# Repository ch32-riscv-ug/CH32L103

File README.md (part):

# CH32L103

<!-- This file is generated from ch32-riscv-ug/ch32-device-data (index/ + evidence/ + pipeline/build/build_readme.py). Edit there, not here. -->

[Choose a part](#product-comparison) &middot; [Documents](#documents) &middot; [Pin maps](#pin-maps--alternate-functions) &middot; [Pin viewer](https://ch32-riscv-ug.github.io/ch32-device-data/pins.html?chip=CH32L103) &middot; [Errata](#errata) &middot; [Examples](#evt-examples) &middot; [Address map](#address-map)

## Quick start

Programming and debug: **2-wire SDI** (WCH-Link, `Serial Debug Interface`).

### Debug / serial defaults

Where these land **without writing a remap register**. SWD is live at reset; the UART pads are not -- the pin must still be put into alternate-function mode. See `route` in evidence/README.ja.md.

| Series | SWDIO | SWCLK | UART TX | UART RX |
|---|---|---|---|---|
| CH32L103 | PA13 | PA14 | PA9 (USART1); PA2 (USART2) | PA10 (USART1); PA3 (USART2) |
| CH32M103 | PA13 | PA14 | PA2 (USART2); PB10 (USART3) | PA3 (USART2); PB11 (USART3) |

### Datasheets and reference manual

- CH32L103DS0.PDF (datasheet): [English](https://ch32-riscv-ug.github.io/CH32L103/datasheet_en/CH32L103DS0.PDF) · [中文](https://ch32-riscv-ug.github.io/CH32L103/datasheet_zh/CH32L103DS0.PDF)
- CH32L103RM.PDF (reference manual): [English](https://ch32-riscv-ug.github.io/CH32L103/datasheet_en/CH32L103RM.PDF) · [中文](https://ch32-riscv-ug.github.io/CH32L103/datasheet_zh/CH32L103RM.PDF)

## Series

| Series | Core | ISA | Flash | SRAM | Main clock | VDD | Packages | Products | Official |
|---|---|---|---|---|---|---|---|---|---|
| **CH32L103** | QingKe V4C | RV32IMAC | 64K | 20K | 96 MHz | 1.8-3.6V | LQFP48,QFN20,QFN32,QSOP28,TSSOP20 | 6 | [en](https://www.wch-ic.com/products/CH32L103.html) / [zh](https://www.wch.cn/products/CH32L103.html) |
| **CH32M103** | QingKe V4C | RV32IMAC | 64K | 20K | 96 MHz | 1.8-3.6V | QSOP28 | 1 | [en](https://www.wch-ic.com/products/CH32M103.html) / [zh](https://www.wch.cn/products/CH32M103.html) |

## Product comparison

### CH32L103 product comparison

Only the 11 rows that differ between these 6 products; the other 14 are the same for all of them.

| | [CH32L103&#8203;C8T6](https://ch32-riscv-ug.github.io/ch32-device-data/pins.html?chip=CH32L103C8T6)&#8203;(LQFP48) | [CH32L103&#8203;F8P6](https://ch32-riscv-ug.github.io/ch32-device-data/pins.html?chip=CH32L103F8P6)&#8203;(TSSOP20) | [CH32L103&#8203;F8U6](https://ch32-riscv-ug.github.io/ch32-device-data/pins.html?chip=CH32L103F8U6)&#8203;(QFN20) | [CH32L103&#8203;G8R6](https://ch32-riscv-ug.github.io/ch32-device-data/pins.html?chip=CH32L103G8R6)&#8203;(QSOP28) | [CH32L103&#8203;K8U6](https://ch32-riscv-ug.github.io/ch32-device-data/pins.html?chip=CH32L103K8U6)&#8203;(QFN32) | [CH32L103&#8203;K8U7](https://ch32-riscv-ug.github.io/ch32-device-data/pins.html?chip=CH32L103K8U7)&#8203;(QFN32) |
|---|---|---|---|---|---|---|
| **GPIO** | 37 | 16 | 19 | 26 | 31 | 31 |
| **Temperature** | -40..85C | -40..85C | -40..85C | -40..85C | -40..85C | -40..105C |
| ADC | 10+3 | 9+3 | 10+3 | 10+3 | 10+3 | 10+3 |
| Tkey | 10 | 9 | 10 | 10 | 10 | 10 |
| CMP | 3 | CMP1 CMP2 | 3 | 3 | 3 | 3 |
| SPI | 2 | SPI1 | 2 | 2 | SPI1 | SPI1 |
| I2C | 2 | I2C1 | 2 | 2 | I2C1 | I2C1 |
| CAN FD | √ | - | - | - | √ | - |
| USB Host Device | Host Device | Device | Host Device | Host Device | Host Device | Host Device |
| USB PD Type-C | DRP Source Sink | DRP Source Sink | DRP Source Sink Built-in Rd(1) | DRP Source Sink | DRP Source Sink Built-in Rd(1) | DRP Source Sink Built-in Rd(1) |
| Main applications and features | General-purpose, Pin compatible | General-purpose, Pin compatible | General-purpose, pin optimized | General-purpose, motor master | General-purpose, pin optimized | General-purpose, pin optimized |

<details><summary>All 25 rows</summary>

| | [CH32L103&#8203;C8T6](https://ch32-riscv-ug.github.io/ch32-device-data/pins.html?chip=CH32L103C8T6)&#8203;(LQFP48) | [CH32L103&#8203;F8P6](https://ch32-riscv-ug.github.io/ch32-device-data/pins.html?chip=CH32L103F8P6)&#8203;(TSSOP20) | [CH32L103&#8203;F8U6](https://ch32-riscv-ug.github.io/ch32-device-data/pins.html?chip=CH32L103F8U6)&#8203;(QFN20) | [CH32L103&#8203;G8R6](https://ch32-riscv-ug.github.io/ch32-device-data/pins.html?chip=CH32L103G8R6)&#8203;(QSOP28) | [CH32L103&#8203;K8U6](https://ch32-riscv-ug.github.io/ch32-device-data/pins.html?chip=CH32L103K8U6)&#8203;(QFN32) | [CH32L103&#8203;K8U7](https://ch32-riscv-ug.github.io/ch32-device-data/pins.html?chip=CH32L103K8U7)&#8203;(QFN32) |
|---|---|---|---|---|---|---|
| **Flash** | 64K | 64K | 64K | 64K | 64K | 64K |
| **SRAM** | 20K | 20K | 20K | 20K | 20K | 20K |
| **GPIO** | 37 | 16 | 19 | 26 | 31 | 31 |
| **Temperature** | -40..85C | -40..85C | -40..85C | -40..85C | -40..85C | -40..105C |
| Advanced-control TIM1 (16-bit) | 1 | 1 | 1 | 1 | 1 | 1 |
| General-purpose TIM2/3 (16-bit) | 2 | 2 | 2 | 2 | 2 | 2 |
| General-purpose TIM4 (32-bit) | 1 | 1 | 1 | 1 | 1 | 1 |
| Low-power timer (LPTIM) | √ | √ | √ | √ | √ | √ |
| Timer Watchdog | 2 ( WWDG + IWDG ) | 2 ( WWDG + IWDG ) | 2 ( WWDG + IWDG ) | 2 ( WWDG + IWDG ) | 2 ( WWDG + IWDG ) | 2 ( WWDG + IWDG ) |
| SysTick (64-bit) | √ | √ | √ | √ | √ | √ |
| RTC | √ | √ | √ | √ | √ | √ |
| ADC | 10+3 | 9+3 | 10+3 | 10+3 | 10+3 | 10+3 |
| Tkey | 10 | 9 | 10 | 10 | 10 | 10 |
| OPA | 1 | 1 | 1 | 1 | 1 | 1 |
| CMP | 3 | CMP1 CMP2 | 3 | 3 | 3 | 3 |
| USART | 4 | 4 | 4 | 4 | 4 | 4 |
| SPI | 2 | SPI1 | 2 | 2 | SPI1 | SPI1 |
| I2C | 2 | I2C1 | 2 | 2 | I2C1 | I2C1 |
| CAN | 1 | 1 | 1 | 1 | 1 | 1 |
| CAN FD | √ | - | - | - | √ | - |
| USB Host Device | Host Device | Device | Host Device | Host Device | Host Device | Host Device |
| USB PD Type-C | DRP Source Sink | DRP Source Sink | DRP Source Sink Built-in Rd(1) | DRP Source Sink | DRP Source Sink Built-in Rd(1) | DRP Source Sink Built-in Rd(1) |
| CPU main frequency | Max: 96MHz | Max: 96MHz | Max: 96MHz | Max: 96MHz | Max: 96MHz | Max: 96MHz |
| Rated voltage | 3.3V | 3.3V | 3.3V | 3.3V | 3.3V | 3.3V |
| Main applications and features | General-purpose, Pin compatible | General-purpose, Pin compatible | General-purpose, pin optimized | General-purpose, motor master | General-purpose, pin optimized | General-purpose, pin optimized |

</details>

## Block diagrams

### CH32L103

System block diagram from the [WCH product page](https://www.wch-ic.com/products/CH32L103.html).

<details><summary>Internal block diagram (datasheet)</summary>

</details>

### CH32M103

System block diagram from the [WCH product page](https://www.wch-ic.com/products/CH32M103.html).

<details><summary>Internal block diagram (datasheet)</summary>

</details>

## Documents

| Document | Kind | English | 中文 |
|---|---|---|---|
| CH32L103DS0.PDF | datasheet | [page](https://www.wch-ic.com/downloads/CH32L103DS0_PDF.html) [mirror](https://ch32-riscv-ug.github.io/CH32L103/datasheet_en/CH32L103DS0.PDF) v2.1 | [page](https://www.wch.cn/downloads/CH32L103DS0_PDF.html) [mirror](https://ch32-riscv-ug.github.io/CH32L103/datasheet_zh/CH32L103DS0.PDF) v2.1 |
| CH32L103RM.PDF | reference-manual | [page](https://www.wch-ic.com/downloads/CH32L103RM_PDF.html) [mirror](https://ch32-riscv-ug.github.io/CH32L103/datasheet_en/CH32L103RM.PDF) v2.2 | [page](https://www.wch.cn/downloads/CH32L103RM_PDF.html) [mirror](https://ch32-riscv-ug.github.io/CH32L103/datasheet_zh/CH32L103RM.PDF) v2.3 |
| CH32L103EVT.ZIP | evt | - | [page](https://www.wch.cn/downloads/CH32L103EVT_ZIP.html) [mirror](https://github.com/ch32-riscv-ug/CH32L103/tree/main/EVT) v2.21 |

### Evaluation boards

- board-manual:en: [CH32L103 Evaluation Board Reference-EN.pdf](https://ch32-riscv-ug.github.io/CH32L103/EVT/PUB/CH32L103%20Evaluation%20Board%20Reference-EN.pdf)
- board-manual:zh: [CH32L103评估板说明书.pdf](https://ch32-riscv-ug.github.io/CH32L103/EVT/PUB/CH32L103%E8%AF%84%E4%BC%B0%E6%9D%BF%E8%AF%B4%E6%98%8E%E4%B9%A6.pdf)
- schematic-pdf: [CH32L103SCH.pdf](https://ch32-riscv-ug.github.io/CH32L103/EVT/PUB/CH32L103SCH.pdf)

5 board schematics under `EVT/PUB/SCHPCB/`: `CH32L103C8T-R0`, `CH32L103F8P-R0`, `CH32L103F8U-R0`, `CH32L103G8R-R0`, `CH32L103K8U-R0`

## Packages & pinout drawings

Pinout drawings are in the datasheet (chapter *Pinouts*); each link opens at the page that carries the drawing:

| Package | Products | Datasheet | Outline |
|---|---|---|---|
| LQFP48 | CH32L103C8T6 | [en](https://ch32-riscv-ug.github.io/CH32L103/datasheet_en/CH32L103DS0.PDF#page=18) / [zh](https://ch32-riscv-ug.github.io/CH32L103/datasheet_zh/CH32L103DS0.PDF#page=13) | [drawing](https://raw.githubusercontent.com/ch32-riscv-ug/WCH-common/main/image/package_LQFP48.png) |
| TSSOP20 | CH32L103F8P6 | [en](https://ch32-riscv-ug.github.io/CH32L103/datasheet_en/CH32L103DS0.PDF#page=19) / [zh](https://ch32-riscv-ug.github.io/CH32L103/datasheet_zh/CH32L103DS0.PDF#page=14) | [drawing](https://raw.githubusercontent.com/ch32-riscv-ug/WCH-common/main/image/package_TSSOP20.png) |
| QFN20 | CH32L103F8U6 | [en](https://ch32-riscv-ug.github.io/CH32L103/datasheet_en/CH32L103DS0.PDF#page=19) / [zh](https://ch32-riscv-ug.github.io/CH32L103/datasheet_zh/CH32L103DS0.PDF#page=14) | [drawing](https://raw.githubusercontent.com/ch32-riscv-ug/WCH-common/main/image/package_QFN20.png) |
| QSOP28 | CH32L103G8R6 | [en](https://ch32-riscv-ug.github.io/CH32L103/datasheet_en/CH32L103DS0.PDF#page=19) / [zh](https://ch32-riscv-ug.github.io/CH32L103/datasheet_zh/CH32L103DS0.PDF#page=14) | [drawing](https://raw.githubusercontent.com/ch32-riscv-ug/WCH-common/main/image/package_QSOP28.png) |
| QFN32 | CH32L103K8U6, CH32L103K8U7 | [en](https://ch32-riscv-ug.github.io/CH32L103/datasheet_en/CH32L103DS0.PDF#page=18) / [zh](https://ch32-riscv-ug.github.io/CH32L103/datasheet_zh/CH32L103DS0.PDF#page=13) | [drawing](https://raw.githubusercontent.com/ch32-riscv-ug/WCH-common/main/image/package_QFN32.png) |
| QSOP28 | CH32M103G8R6 | [en](https://ch32-riscv-ug.github.io/CH32L103/datasheet_en/CH32L103DS0.PDF#page=20) / [zh](https://ch32-riscv-ug.github.io/CH32L103/datasheet_zh/CH32L103DS0.PDF#page=15) | [drawing](https://raw.githubusercontent.com/ch32-riscv-ug/WCH-common/main/image/package_QSOP28.png) |

## Pin maps & alternate functions

> [!NOTE]
> These are the **pin-table superset**: the datasheet prints one pad table for every product that shares a pinout, so a pad row does not mean this part has the peripheral. Use the product comparison table above for what a given part number contains.

### CH32L103 pin map

Pin functions (filterable): [ALL](https://ch32-riscv-ug.github.io/ch32-device-data/pins.html?chip=CH32L103) [ADC](https://ch32-riscv-ug.github.io/ch32-device-data/pins.html?chip=CH32L103&features=ADC) [I2C](https://ch32-riscv-ug.github.io/ch32-device-data/pins.html?chip=CH32L103&features=I2C) [SPI](https://ch32-riscv-ug.github.io/ch32-device-data/pins.html?chip=CH32L103&features=SPI) [SYS](https://ch32-riscv-ug.github.io/ch32-device-data/pins.html?chip=CH32L103&features=SYS) [TIM](https://ch32-riscv-ug.github.io/ch32-device-data/pins.html?chip=CH32L103&features=TIM) [UART](https://ch32-riscv-ug.github.io/ch32-device-data/pins.html?chip=CH32L103&features=UART) [USB](https://ch32-riscv-ug.github.io/ch32-device-data/pins.html?chip=CH32L103&features=USB)

<details><summary><b>CH32L103 pin map</b> (44 pads x 6 products)</summary>

| Pin name | Type | [CH32L103&#8203;C8T6](https://ch32-riscv-ug.github.io/ch32-device-data/pins.html?chip=CH32L103C8T6)&#8203;(LQFP48) | [CH32L103&#8203;F8P6](https://ch32-riscv-ug.github.io/ch32-device-data/pins.html?chip=CH32L103F8P6)&#8203;(TSSOP20) | [CH32L103&#8203;F8U6](https://ch32-riscv-ug.github.io/ch32-device-data/pins.html?chip=CH32L103F8U6)&#8203;(QFN20) | [CH32L103&#8203;G8R6](https://ch32-riscv-ug.github.io/ch32-device-data/pins.html?chip=CH32L103G8R6)&#8203;(QSOP28) | [CH32L103&#8203;K8U6](https://ch32-riscv-ug.github.io/ch32-device-data/pins.html?chip=CH32L103K8U6)&#8203;(QFN32) | [CH32L103&#8203;K8U7](https://ch32-riscv-ug.github.io/ch32-device-data/pins.html?chip=CH32L103K8U7)&#8203;(QFN32) | Notes |
|---|---|---|---|---|---|---|---|---|
| PA1 | I/O/A | 11 | 7 | 2 | 10 | 7 | 7 |  |
| PA2 | I/O/A | 12 | 8 | 3 | 11 | 8 | 8 | UART TX (USART2) |
| PA3 | I/O/A | 13 | 9 | 4 | 12 | 9 | 9 | UART RX (USART2) |
| PA4 | I/O/A | 14 | 10 | 5 | 13 | 10 | 10 |  |
| PA5 | I/O/A | 15 | 11 | 6 | 14 | 11 | 11 |  |
| PA6 | I/O/A | 16 | 12 | 20 | 15 | 12 | 12 |  |
| PA7 | I/O/A | 17 | 13 | 7 | 17 | 13 | 13 |  |
| PA8 | I/O | 29 | - | 14 | 24 | 18 | 18 |  |
| PA9 | I/O | 30 | - | 15 | 25 | 19 | 19 | UART TX (USART1) |
| PA10 | I/O | 31 | - | 18 | 26 | 20 | 20 | UART RX (USART1) |
| PA11 | I/O | 32 | 17 | 17 | 27 | 21 | 21 |  |
| PA12 | I/O | 33 | 18 | 16 | 28 | 22 | 22 |  |
| PA13 | I/O | 34 | 19 | 17 | 28 | 23 | 23 | SWDIO |
| PA14 | I/O | 37 | 20 | 16 | 1 | 24 | 24 | SWCLK |
| PA15 | I/O | 38 | - | - | - | 25 | 25 |  |
| PB0 | I/O/A | 18 | - | 8 | 16 | 14 | 14 | UART TX (USART4) |
| PB1 | I/O/A | 19 | 14 | 9 | 18 | 15 | 15 | UART RX (USART4) |
| PB2 | I/O/A | 20 | - | - | - | 16 | 16 |  |
| PB3 | I/O/A | 39 | - | - | 4 | 26 | 26 |  |
| PB4 | I/O/A | 40 | - | - | - | 27 | 27 |  |
| PB5 | I/O/A | 41 | - | - | 1 | 28 | 28 |  |
| PB6 | I/O/A | 42 | 19 | 11 | 2 | 29 | 29 |  |
| PB7 | I/O/A | 43 | 20 | 18 | 3 | 30 | 30 |  |
| PB8 | I/O/A | 45 | 1 | - | 5 | 32 | 32 |  |
| PB9 | I/O | 46 | - | - | - | 31 | 31 |  |
| PB10 | I/O/A | 21 | - | 9 | 18 | - | - | UART TX (USART3) |
| PB11 | I/O/A | 22 | - | 10 | 19 | - | - | UART RX (USART3) |
| PB12 | I/O | 25 | - | - | 20 | - | - |  |
| PB13 | I/O | 26 | - | 11 | 21 | - | - |  |
| PB14 | I/O/A | 27 | - | 12 | 22 | - | - |  |
| PB15 | I/O/A | 28 | - | 13 | 23 | 17 | 17 |  |
| BOOT0 | I | 44 | 1 | - | - | 31 | 31 |  |
| NRST | I | 7 | 4 | - | - | - | - |  |
| OSC_IN | I/O/A | 5 | 2 | - | 8 | 4 | 4 | OSC |
| OSC_OUT | I/O/A | 6 | 3 | - | - | 5 | 5 | OSC |
| PA0-WKUP | I/O/A | 10 | 6 | 1 | 9 | 6 | 6 |  |
| PC13-TAMPER-RTC | I/O | 2 | - | - | - | - | - |  |
| PC14-OSC32_IN | I/O/A | 3 | - | - | - | 2 | 2 | OSC |
| PC15-OSC32_OUT | I/O/A | 4 | - | - | - | 3 | 3 | OSC |
| VBAT | P | 1 | - | - | - | - | - |  |
| VDD | P | 24/36/48 | 16 | 19 | 6 | 1 | 1 |  |
| VDDA | P | 9 | 5 | - | - | - | - |  |
| VSS | P | 23/35/47 | 15 | EP | 7 | EP | EP |  |
| VSSA | P | 8 | - | - | - | - | - |  |

</details>

<details><summary><b>CH32L103 alternate functions</b></summary>

| Pad | default | (no route stated) | remap-1 | remap-2 | remap-3 | remap-4 | remap-5 | remap-7 |
|---|---|---|---|---|---|---|---|---|
| PA1 | ADC_IN1, OPA_N4, TIM2_CH2, USART2_RTS | - | - | TIM1_CH1, TIM2_CH2, USART2_RTS | TIM1_CH1, USART2_RTS | - | TIM1_CH2N | - |
| PA2 | ADC_IN2, CMP1_P0, OPA_O2, TIM2_CH3, USART2_TX | - | TIM2_CH3 | USART1_CTS | - | TIM1_CH4, TIM2_CH2 | TIM2_CH2 | - |
| PA3 | ADC_IN3, OPA_O0, TIM2_CH4, USART2_RX | - | TIM2_CH4 | USART1_CK | TIM1_ETR | TIM2_CH1_ETR | TIM1_CH4 | - |
| PA4 | ADC_IN4, OPA_O3, SPI1_NSS, USART2_CK | - | - | USART1_TX, USART2_CK | USART1_RX, USART2_CK | - | - | TIM2_CH4 |
| PA5 | ADC_IN5, OPA_N3, SPI1_SCK | - | USART4_TX | USART1_RX | USART1_TX | - | - | TIM2_CH3 |
| PA6 | ADC_IN6, OPA_N1, OPA_P5, SPI1_MISO, TIM3_CH1 | - | TIM1_BKIN, USART4_CK | - | USART1_CK | TIM2_CH4, USART1_CK | TIM2_CH4 | - |
| PA7 | ADC_IN7, OPA_N5, OPA_P3, SPI1_MOSI, TIM3_CH2 | - | TIM1_CH1N, USART4_CTS | TIM1_CH2 | TIM1_CH2 | - | - | - |
| PA8 | MCO, TIM1_CH1, USART1_CK | - | TIM1_CH1, USART1_CK | - | - | - | - | - |
| PA9 | TIM1_CH2, USART1_TX | - | TIM1_CH2 | - | - | - | - | - |
| PA10 | TIM1_CH3, USART1_RX | - | TIM1_CH3 | - | - | - | - | - |
| PA11 | CAN1_RX, TIM1_CH4, USART1_CTS, USBDM | - | TIM1_CH4, USART1_CTS | USART2_TX | USART2_RX | - | - | - |
| PA12 | CAN1_TX, TIM1_ETR, USART1_RTS, USBDP | - | TIM1_ETR, USART1_RTS | I2C1_SDA, SPI1_NSS, USART2_RX | USART2_TX | TIM1_BKIN | TIM1_BKIN, TIM2_CH1_ETR, USART1_RX | TIM2_CH1_ETR |
| PA13 | - | - | - | I2C1_SCL, TIM1_BKIN, USART1_RTS | TIM1_BKIN | USART1_RTS | TIM1_ETR | - |
| PA14 | - | - | - | TIM1_CH3 | TIM1_CH3 | TIM1_CH1N, USART1_CTS | TIM1_CH1N | - |
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
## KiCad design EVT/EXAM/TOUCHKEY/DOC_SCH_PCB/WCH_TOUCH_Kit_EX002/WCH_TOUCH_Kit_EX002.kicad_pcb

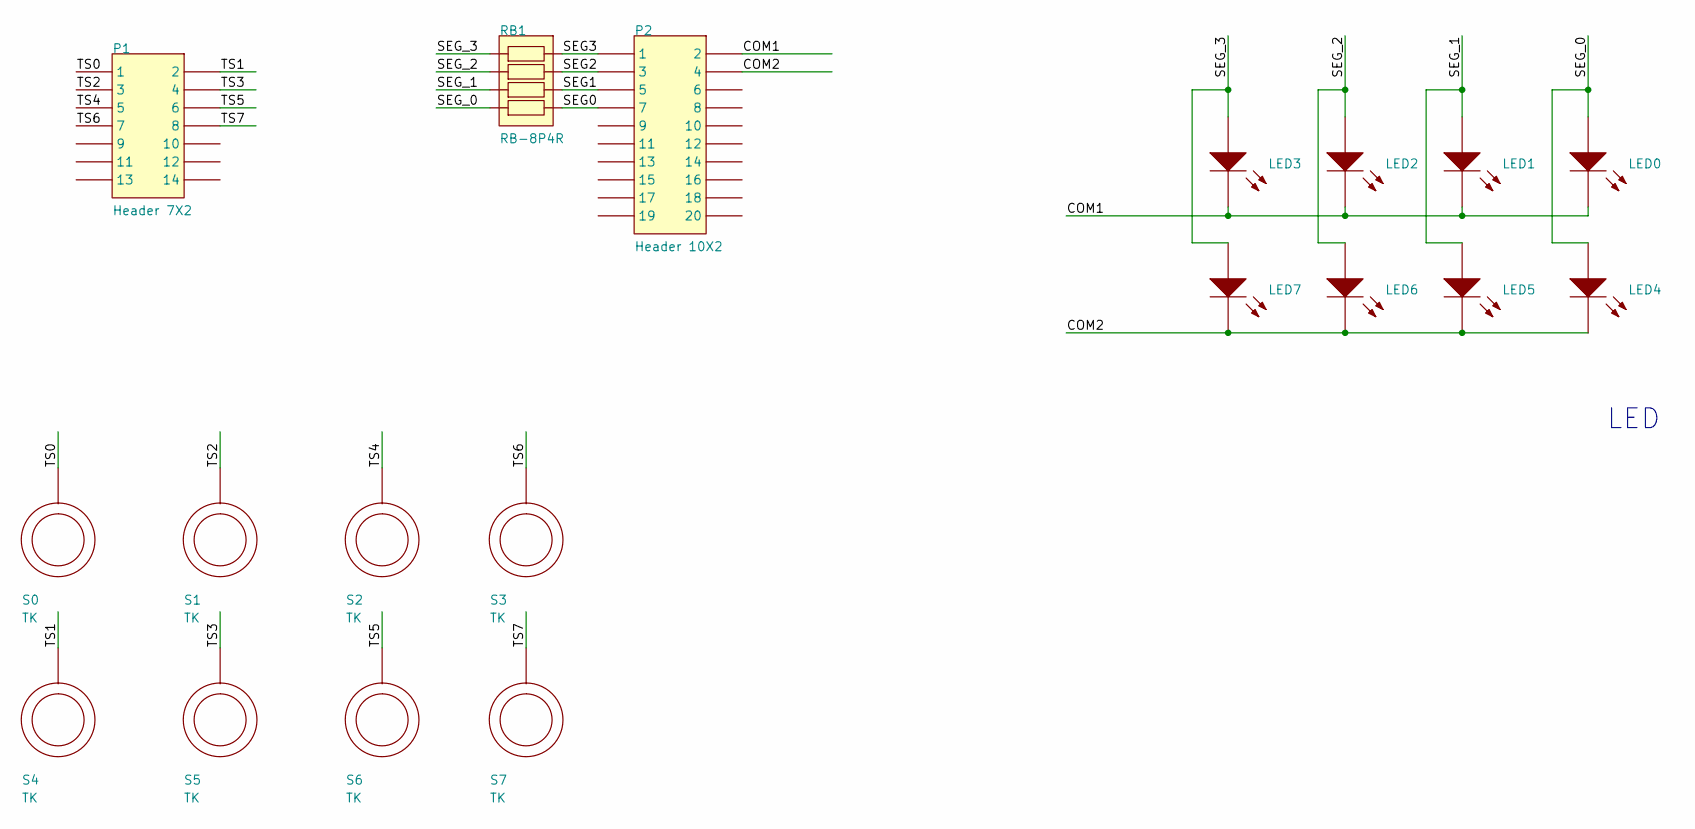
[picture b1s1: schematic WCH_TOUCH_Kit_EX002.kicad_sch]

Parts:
LED0, LED1, LED2, LED3, LED4, LED5, LED6, LED7: LED0805-RD_EH
P1: Header 7X2; HDR-TH_14P-P2.54-H-F-R2-C10-W8.5
P2: Header 10X2; HDR-TH_20P-P2.54-H-F-R2-C10-W8.5
RB1: RB-8P4R; RCA-8P4R-0603
S0, S1, S2, S3, S4, S5, S6, S7: TK; TOUCHKEY-12mm-S

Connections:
COM1: LED0.2 (K), LED1.2 (K), LED2.2 (K), LED3.2 (K), P2.2
COM2: LED4.2 (K), LED5.2 (K), LED6.2 (K), LED7.2 (K), P2.4
SEG0: P2.7, RB1.4
SEG1: P2.5, RB1.3
SEG2: P2.3, RB1.2
SEG3: P2.1, RB1.1
SEG_0: LED0.1 (A), LED4.1 (A), RB1.5
SEG_1: LED1.1 (A), LED5.1 (A), RB1.6
SEG_2: LED2.1 (A), LED6.1 (A), RB1.7
SEG_3: LED3.1 (A), LED7.1 (A), RB1.8
TS0: P1.1, S0.1
TS1: P1.2, S4.1
TS2: P1.3, S1.1
TS3: P1.4, S5.1
TS4: P1.5, S2.1
TS5: P1.6, S6.1
TS6: P1.7, S3.1
TS7: P1.8, S7.1

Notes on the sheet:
LED

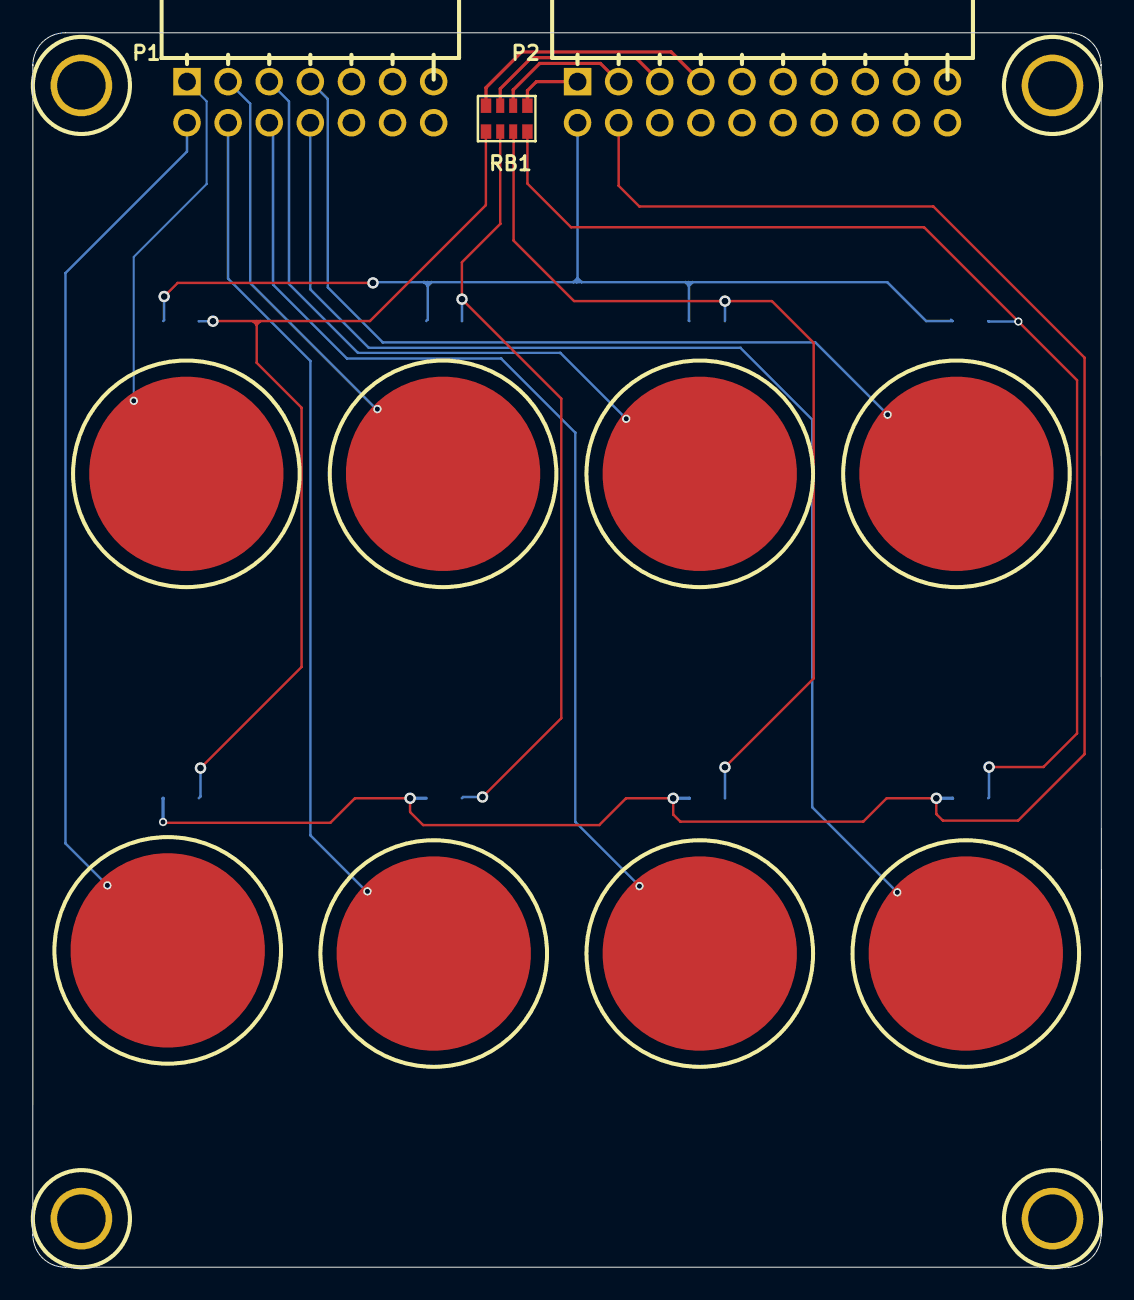
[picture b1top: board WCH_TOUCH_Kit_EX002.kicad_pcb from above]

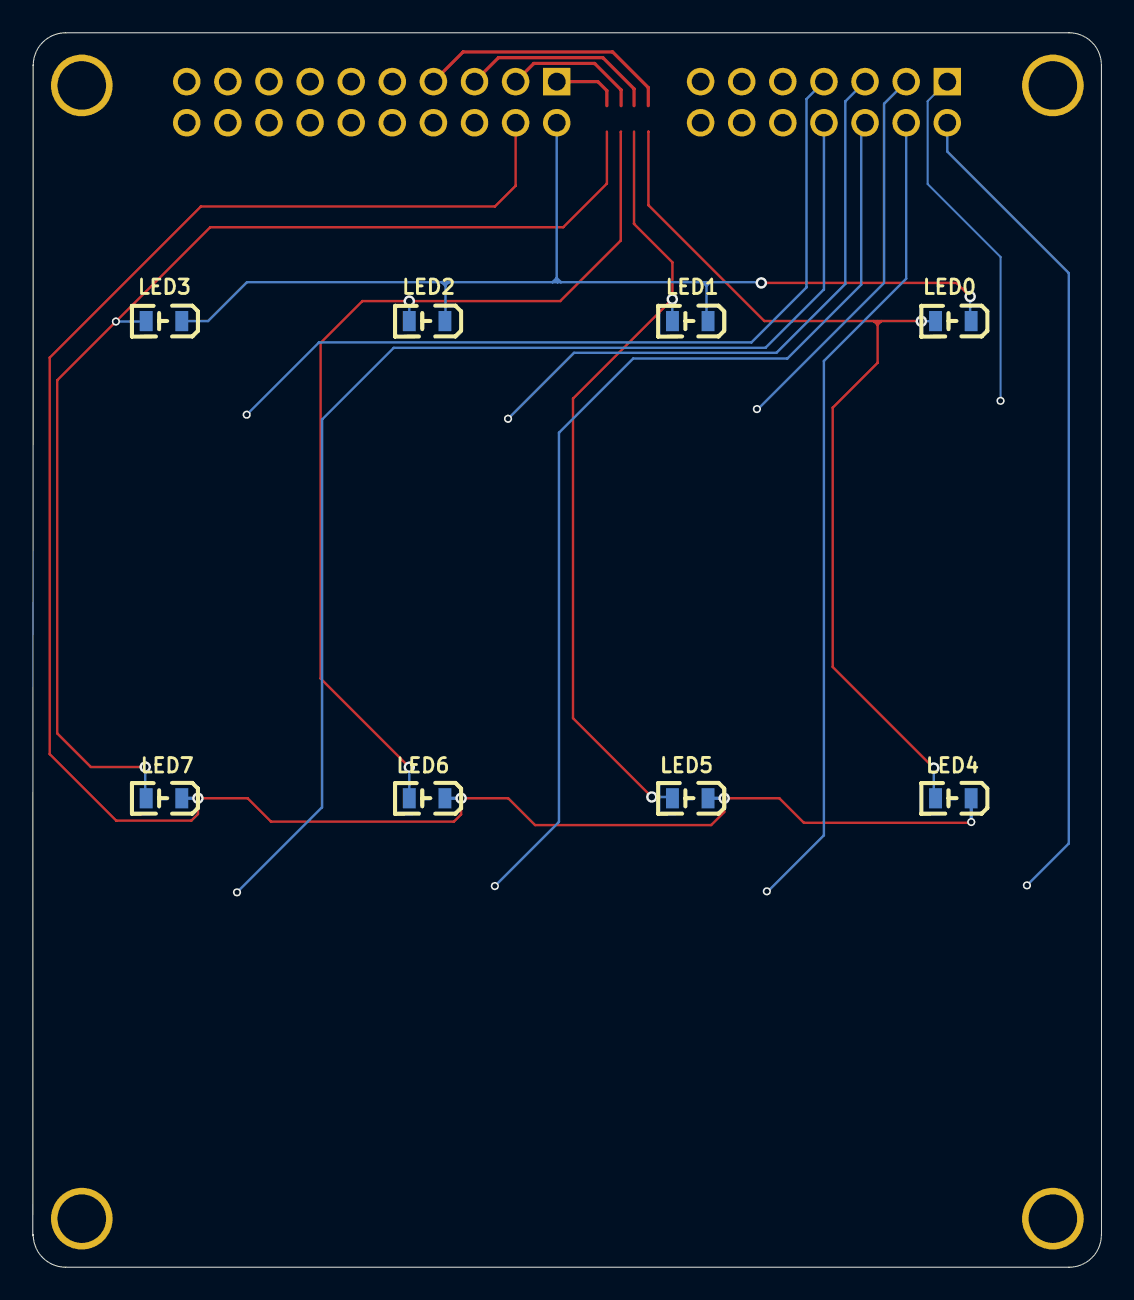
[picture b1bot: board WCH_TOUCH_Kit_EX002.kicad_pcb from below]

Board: 2 copper layers, 66.0 x 76.3 mm, 19 parts (8 on the bottom side), 18 nets.

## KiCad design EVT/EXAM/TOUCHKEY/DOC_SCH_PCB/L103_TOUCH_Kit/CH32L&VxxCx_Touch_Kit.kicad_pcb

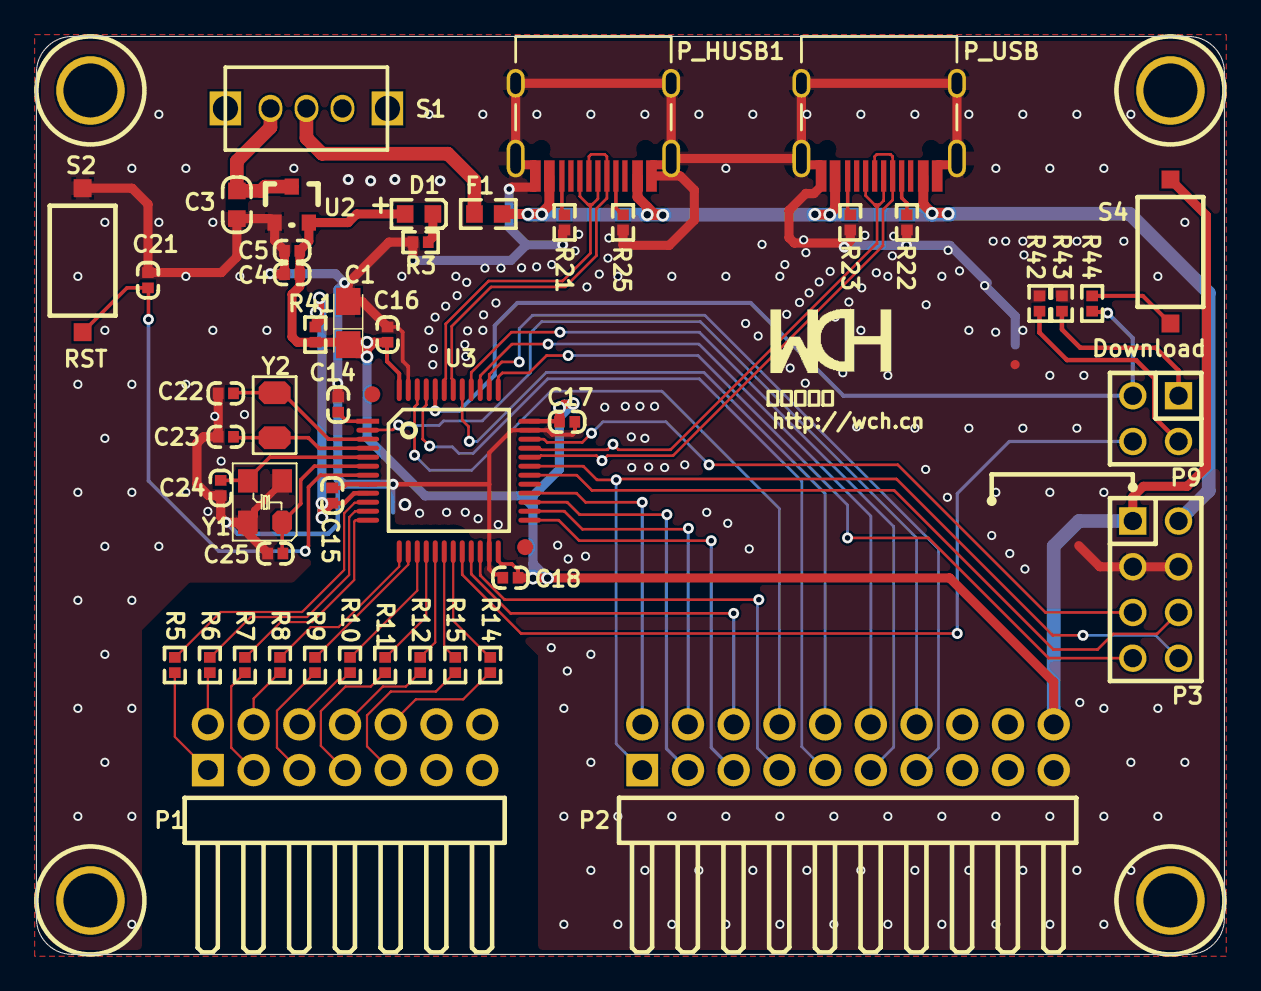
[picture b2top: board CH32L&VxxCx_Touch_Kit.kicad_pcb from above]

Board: 2 copper layers, 66.0 x 51.0 mm, 48 parts (0 on the bottom side), 63 nets.

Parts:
C1: 10uF; CASE-A_3216
C3: 10uF; 0603_C
C4: 2.2uF; 0402_C
C5, C14, C15, C16, C17, C18, C21: 0.1uF; 0402_C
C22, C23: 12pF; 0402_C
C24, C25: 22pF; 0402_C
D1: power; 0603+
F1: 500mA; 0603
P1: Header 7X2; HDR-TH_14P-P2.54-H-M-R2-C10-S2.54
P2: Header 10X2; HDR-TH_20P-P2.54-H-M-R2-C10-S2.54
P3: Header 4X2; IDC8-2.54mm
P9: Header 2X2; IDC4-2.54mm
P_HUSB1: TYPE-C; TYPE-C-Receptacle-2.0
P_USB: TYPE-C; TYPE-C-Receptacle-2.0
R3, R44: 1K; 0402
R5, R6, R7, R8, R9, R10, R11, R12, R14, R15: 0Ω(560Ω); 0402
R21, R25: 5.1K; 0402
R22, R23: NC(5.1K); 0402
R41: 0Ω; 0402
R42, R43: 10K; 0402
S1: SW SPDT; SW1
S2: RST; SMD_6.1x3.65x2.5mm-KEY
S4: Download; SMD_6.1x3.65x2.5mm-KEY
U2: 6219P33M; SOT-23
U3: CH32V203CxT; LQFP48
Y1: 8M; XT3225
Y2: 32.768k; FC-135

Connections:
3V3: C1.1, C4.1, C5.1, C16.2, C17.2, C18.2, D1.1, P2.20, P3.1, R41.1, S4.1, U2.2, U3.24, U3.36, U3.48
+5V: F1.1, P3.2, P_HUSB1.A4, P_HUSB1.B4, P_USB.A4, P_USB.B4
BOOT0: P9.3, R44.1, U3.44
BOOT1: P9.4, U3.20
GND: C1.2, C3.2, C4.2, C5.2, C14.2, C15.2, C16.1, C17.1, C18.1, C21.1, C22.2, C23.2, C24.1, C25.1, P2.19, P3.3, P3.4, P_HUSB1.0, P_HUSB1.A1, P_HUSB1.B1, P_USB.0, P_USB.A1, P_USB.B1, R3.2, R21.2, R22.2, R23.2, R25.2, R42.2, R43.2, S2.1, U2.1, U3.8, U3.23, U3.35, U3.47, Y1.2, Y1.4
NRST: C21.2, S2.2, U3.7
NetD1_2: D1.2, R3.1
NetF1_2: F1.2, S1.1
NetP9_1: P9.1, R43.1
NetP9_2: P9.2, R42.1
NetP_HUSB1_A5: P_HUSB1.A5, R25.1
NetP_HUSB1_B5: P_HUSB1.B5, R21.1
NetP_USB_A5: P_USB.A5, R22.1
NetP_USB_B5: P_USB.B5, R23.1
NetR44_2: R44.2, S4.2
PA0: R5.1, U3.10
PA1: R6.2, U3.11
PA2: R7.1, U3.12
PA3: R8.2, U3.13
PA4: R9.1, U3.14
PA5: R10.2, U3.15
PA6: R11.1, U3.16
PA7: R12.2, U3.17
PA9: P3.6, U3.30
PA10: P2.1, P3.8, U3.31
PA11: P_USB.A7, P_USB.B7, U3.32
PA12: P_USB.A6, P_USB.B6, U3.33
PA13: P3.5, U3.34
PA14: P3.7, U3.37
PA15: P2.13, U3.38
PB0: R15.1, U3.18
PB1: R14.2, U3.19
PB3: P2.12, U3.39
PB4: P2.11, U3.40
PB5: P2.10, U3.41
PB6: P_HUSB1.A7, P_HUSB1.B7, U3.42
PB7: P_HUSB1.A6, P_HUSB1.B6, U3.43
PB8: P2.9, U3.45
PB9: P2.8, U3.46
PB10: P2.6, U3.21
PB11: P2.7, U3.22
PB12: P2.5, U3.25
PB13: P2.4, U3.26
PB14: P2.3, U3.27
PB15: P2.2, U3.28
PC13: P2.14, U3.2
PC14: C22.1, U3.3, Y2.1
PC15: C23.1, U3.4, Y2.2
PD0: C24.2, U3.5, Y1.3
PD1: C25.2, U3.6, Y1.1
TS0: P1.1, R5.2
TS1: P1.2, R6.1
TS2: P1.3, R7.2
TS3: P1.4, R8.1
TS4: P1.5, R9.2
TS5: P1.6, R10.1
TS6: P1.7, R11.2
TS7: P1.8, R12.1
TS8: P1.9, R15.2
TS9: P1.10, R14.1
V5V: C3.1, S1.2, U2.3
VBAT: C14.1, U3.1
VDDA: C15.1, R41.2, U3.9

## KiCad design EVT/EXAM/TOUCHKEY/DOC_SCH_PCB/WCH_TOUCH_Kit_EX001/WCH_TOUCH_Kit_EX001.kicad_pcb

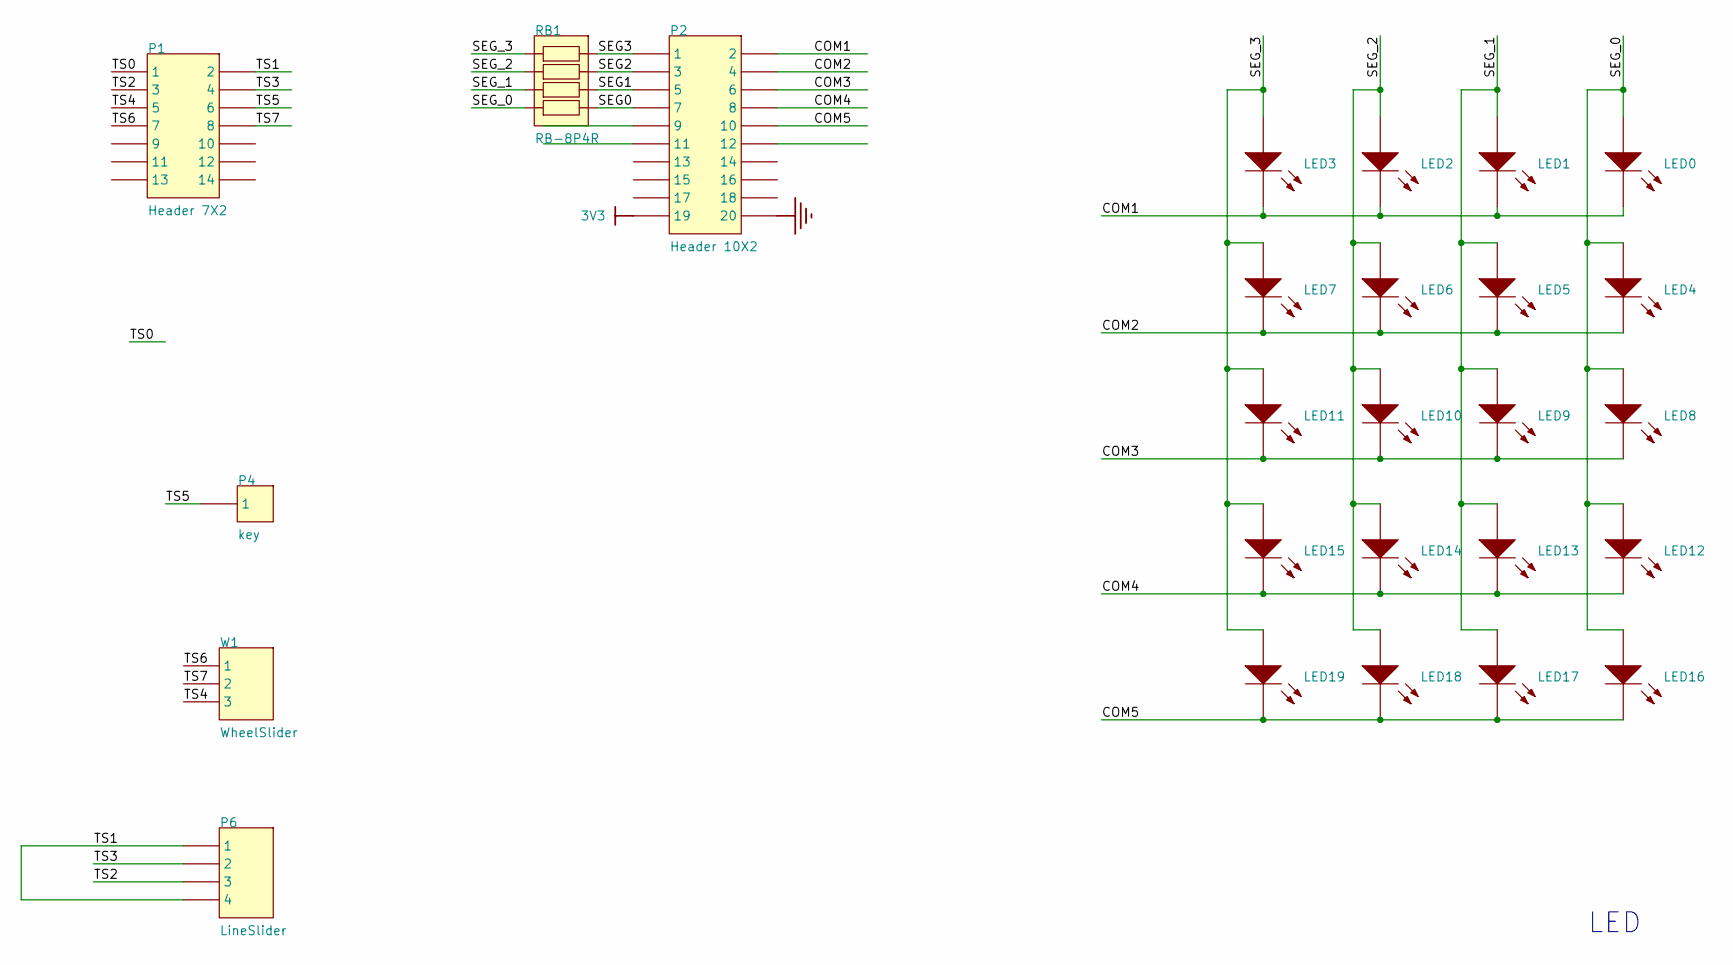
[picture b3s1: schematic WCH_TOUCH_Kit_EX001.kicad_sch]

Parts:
LED0, LED1, LED2, LED3, LED4, LED5, LED6, LED7, LED8, LED9, LED10, LED11, LED12, LED13, LED14, LED15, LED16, LED17, LED18, LED19: LED0805-RD_EH
P1: Header 7X2; HDR-TH_14P-P2.54-H-F-R2-C10-W8.5
P2: Header 10X2; HDR-TH_20P-P2.54-H-F-R2-C10-W8.5
P4: key
P6: LineSlider; Slider_4_46X8.5
RB1: RB-8P4R; RCA-8P4R-0603
W1: WheelSlider; 滑轮10-18-3

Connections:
3V3: P2.19
COM1: LED0.2 (K), LED1.2 (K), LED2.2 (K), LED3.2 (K), P2.2
COM2: LED4.2 (K), LED5.2 (K), LED6.2 (K), LED7.2 (K), P2.4
COM3: LED8.2 (K), LED9.2 (K), LED10.2 (K), LED11.2 (K), P2.6
COM4: LED12.2 (K), LED13.2 (K), LED14.2 (K), LED15.2 (K), P2.8
COM5: LED16.2 (K), LED17.2 (K), LED18.2 (K), LED19.2 (K), P2.10
GND: P2.20
SEG0: P2.7, RB1.4
SEG1: P2.5, RB1.3
SEG2: P2.3, RB1.2
SEG3: P2.1, RB1.1
SEG_0: LED0.1 (A), LED4.1 (A), LED8.1 (A), LED12.1 (A), LED16.1 (A), RB1.5
SEG_1: LED1.1 (A), LED5.1 (A), LED9.1 (A), LED13.1 (A), LED17.1 (A), RB1.6
SEG_2: LED2.1 (A), LED6.1 (A), LED10.1 (A), LED14.1 (A), LED18.1 (A), RB1.7
SEG_3: LED3.1 (A), LED7.1 (A), LED11.1 (A), LED15.1 (A), LED19.1 (A), RB1.8
TS0: P1.1
TS1: P1.2, P6.1, P6.4
TS2: P1.3, P6.3
TS3: P1.4, P6.2
TS4: P1.5, W1.3
TS5: P1.6, P4.1
TS6: P1.7, W1.1
TS7: P1.8, W1.2

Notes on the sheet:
LED

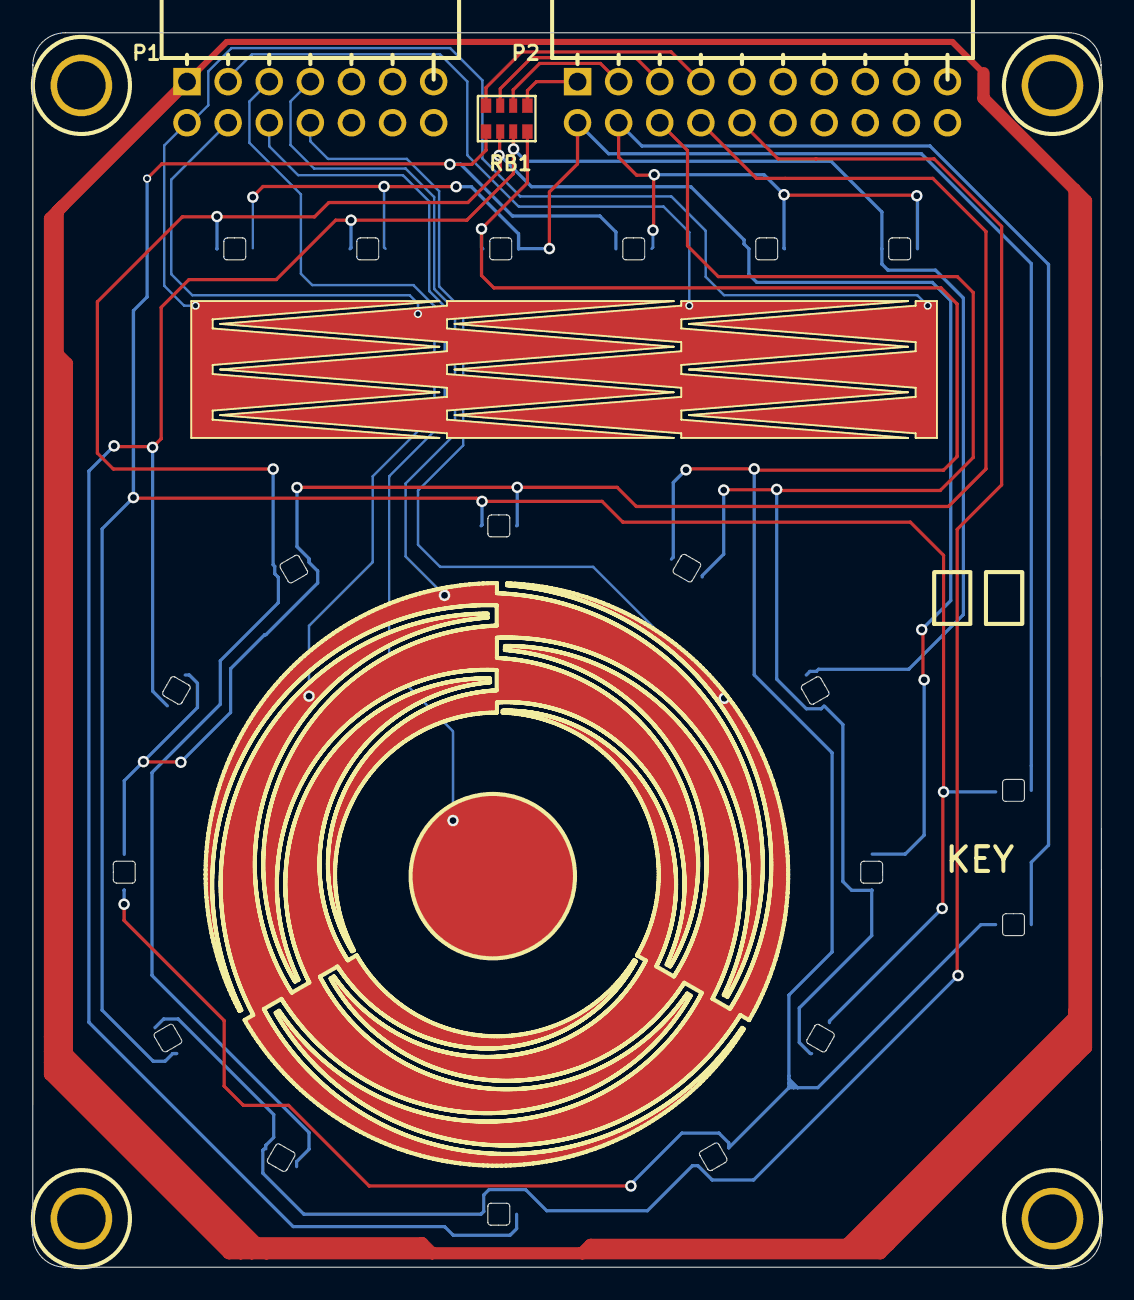
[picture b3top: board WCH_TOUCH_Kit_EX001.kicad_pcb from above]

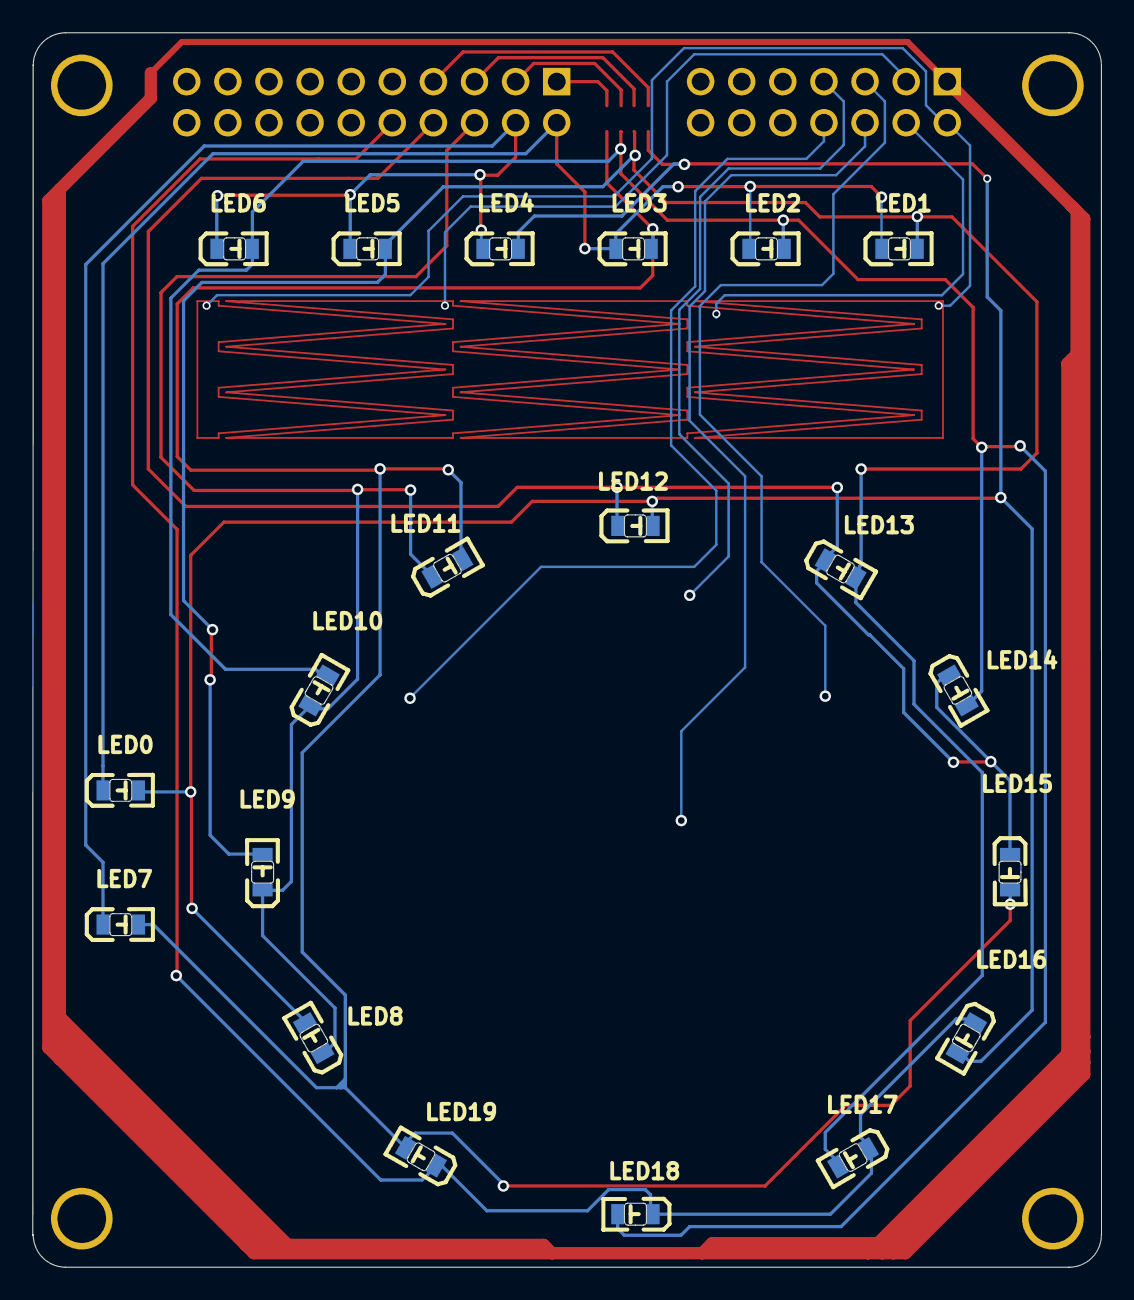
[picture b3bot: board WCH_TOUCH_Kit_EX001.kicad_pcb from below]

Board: 2 copper layers, 66.0 x 76.3 mm, 26 parts (20 on the bottom side), 20 nets.

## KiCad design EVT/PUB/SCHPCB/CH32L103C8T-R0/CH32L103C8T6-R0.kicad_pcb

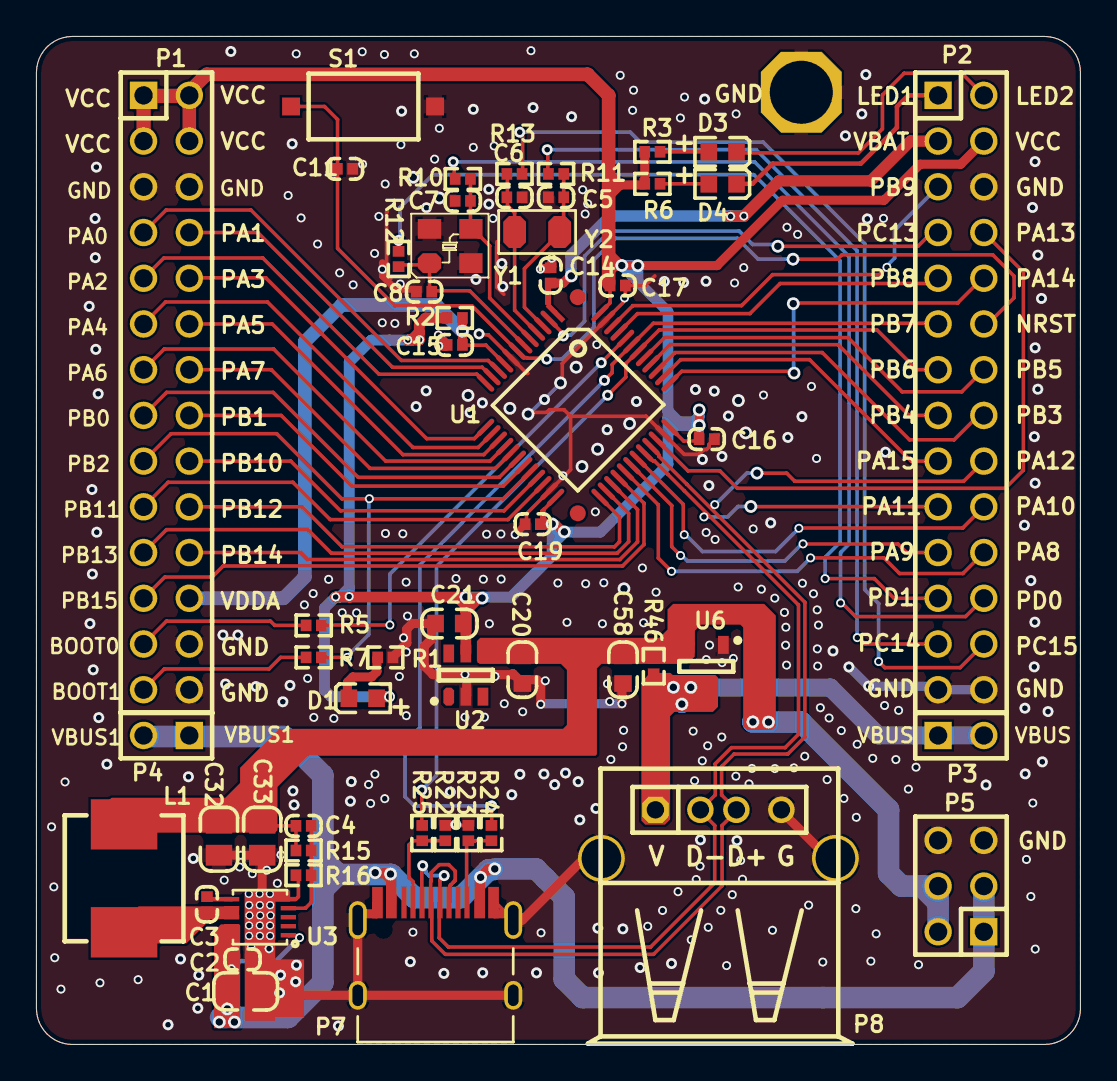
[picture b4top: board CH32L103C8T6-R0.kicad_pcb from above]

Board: 2 copper layers, 58.0 x 56.0 mm, 54 parts (0 on the bottom side), 62 nets.

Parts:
C1: NC(22uF/35V); 0805_C
C2: NC(0.1uF); 0402_C
C3: NC(100nF); 0402_C
C4: NC(68pF); 0402_C
C5, C6: 12pF; 0402_C
C7, C8: 22pF; 0402_C
C11, C14, C15, C16, C17, C19: 0.1uF; 0402_C
C20, C21, C58: 10uF; 0603_C
C32, C33: NC(22uF); 0805_C
D1: RED; 0603+
D3: LED2; 0603+
D4: LED1; 0603+
L1: NC(4.7uH); IND-SMD_L7.0-W6.6
P1, P2: HEADER 14x2; IDC28-2.54MM
P3, P4: HEADER 2; SIP2-2.54mm
P5: HEADER 3x2; IDC6-2.54mm
P7: TYPE-C; TYPE-C-Receptacle-2.0
P8: USB_A; USBAF
R1, R3, R6: 1K; 0402
R2, R24, R25: 0Ω; 0402
R5, R7: 10K; 0402
R10, R11, R12, R13, R46: NC(0Ω); 0402
R15: NC(15K); 0402
R16: NC(4.7K); 0402
R22, R23: 5.1K; 0402
S1: KEY; SMD_6.1x3.65x2.5mm-KEY
U1: CH32L103C8T; LQFP48
U2: CH2003K; SOT-23-6
U3: NC(CH2024Q); DFN10_3X3
U6: CH213; SOT-23-3
Y1: 8M; XT3225
Y2: 32.768k; FC-135

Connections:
3V3: C16.1, C17.2, C19.2, C21.2, D1.1, P1.1, P1.2, P1.3, P1.4, P2.4, R2.1, R3.1, R6.1, U1.24, U1.36, U1.48, U2.5
+5V: C4.1, C20.2, C32.2, C33.2, C58.1, L1.2, P5.2, P5.4, R15.2, R46.1, U2.4, U6.2
BOOT0: R5.1, U1.44
BOOT1: P1.17, R7.1, U1.20
CC1: P2.13, R25.2, U1.42
CC2: P2.11, R24.1, U1.43
FB: C4.2, R15.1, R16.2, U3.4
GND: C1.1, C2.1, C5.2, C6.2, C7.1, C8.1, C11.1, C14.2, C15.2, C16.2, C17.1, C19.1, C20.1, C21.1, C32.1, C33.1, C58.2, P1.5, P1.6, P1.26, P1.28, P2.6, P2.27, P2.28, P5.5, P5.6, P7.0, P7.A1, P7.B1, P8.0, P8.4, R1.2, R16.1, R22.2, R23.2, S1.2, U1.8, U1.23, U1.35, U1.47, U2.2, U3.0, U3.5, U6.1, Y1.2, Y1.4
LED1: D4.2, P2.1
LED2: D3.2, P2.2
NRST: C11.2, P2.12, S1.1, U1.7
NetC3_1: C3.1, U3.6
NetC3_2: C3.2, L1.1, U3.7, U3.8
NetD1_2: D1.2, R1.1
NetD3_1: D3.1, R3.2
NetD4_1: D4.1, R6.2
NetP1_25: P1.25, R5.2
NetP1_27: P1.27, R7.2
NetP7_A5: P7.A5, R22.1, R25.1
NetP7_B5: P7.B5, R23.1, R24.2
OSCI: C5.1, R11.2, U1.3, Y2.1
OSCO: C6.1, R13.2, U1.4, Y2.2
PA0: P1.7, U1.10
PA1: P1.8, U1.11
PA2: P1.9, U1.12
PA3: P1.10, U1.13
PA4: P1.11, U1.14
PA5: P1.12, U1.15
PA6: P1.13, U1.16
PA7: P1.14, U1.17
PA8: P2.22, U1.29
PA9: P2.21, U1.30
PA10: P2.20, U1.31
PA11: P2.19, P7.A7, P7.B7, P8.2, U1.32
PA12: P2.18, P7.A6, P7.B6, P8.3, U1.33
PA13: P2.8, U1.34
PA14: P2.10, U1.37
PA15: P2.17, U1.38
PB0: P1.15, U1.18
PB1: P1.16, U1.19
PB3: P2.16, U1.39
PB4: P2.15, U1.40
PB5: P2.14, U1.41
PB8: P2.9, U1.45
PB9: P2.5, U1.46
PB10: P1.18, U1.21
PB11: P1.19, U1.22
PB12: P1.20, U1.25
PB13: P1.21, U1.26
PB14: P1.22, U1.27
PB15: P1.23, U1.28
PC13: P2.7, U1.2
PC14: P2.25, R11.1
PC15: P2.26, R13.1
PD0: P2.24, R10.1
PD1: P2.23, R12.1
VBAT: C14.1, P2.3, U1.1
VBUS: P3.1, P3.2, P8.1, R46.2, U6.3
VBUS1: C1.2, C2.2, P4.1, P4.2, P5.1, P5.3, P7.A4, P7.B4, U3.1, U3.9, U3.10
VDDA: C15.1, P1.24, R2.2, U1.9
XI: C7.2, R10.2, U1.5, Y1.3
XO: C8.2, R12.2, U1.6, Y1.1

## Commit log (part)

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2026-06-15 update update.sh and add GitHub Actions workflow for automated datasheet downloads
2026-06-15 update cron schedule in GitHub Actions workflow and enhance download script with retry logic
2026-06-15 refactor update job to simplify commit logic in GitHub Actions workflow
2026-06-16 update GitHub Actions schedule
2026-06-19 update GitHub Actions workflow to implement keepalive logic and remove unnecessary permissions
2026-06-19 refactor fetch function in update.sh to simplify error handling and remove retry logic
